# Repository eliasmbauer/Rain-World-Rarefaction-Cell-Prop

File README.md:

# Rain World Rarefaction Cell Interactive Prop

Notice: This project is currently unfinished, and will be updated regularly until it's completion.

In this folder you should find everything you need to get started with assembling this project yourself.  
`setup.pdf` should contain the step-by-step instructions to build this project from scratch using the design files provided.  
Consider `README.md` as a folder hierarchy list, as well as a description of what exactly this is for those of you unfamiliar with the video game *Rain World*.

# What is it?

This project is a physical recreation of the Rarefaction Cell from the video game *Rain World*, an orb-like object that can alter the gravity of the character in-game.

# Folder Contents
- **setup.pdf** 
  A PDF containing the assembly instructions.

- **Rarefaction_Cell_Chassis** 
  A folder containing the stl files for the chassis, modeled after the in-game asset.

- **Refraction_Cell_Circuit_(Kicad)** 
  A folder containing the Gerber files necessary to edit and print the control board, as well as the files necessary for modifications.

- **Rarefaction_Cell_Firmware** 
  A folder containing firmware for flashing the onboard ESP32.

- **Refraction_Cell_Audio_Bytes**
  A folder containing all the audio samples and raw audio bytes used in this project.

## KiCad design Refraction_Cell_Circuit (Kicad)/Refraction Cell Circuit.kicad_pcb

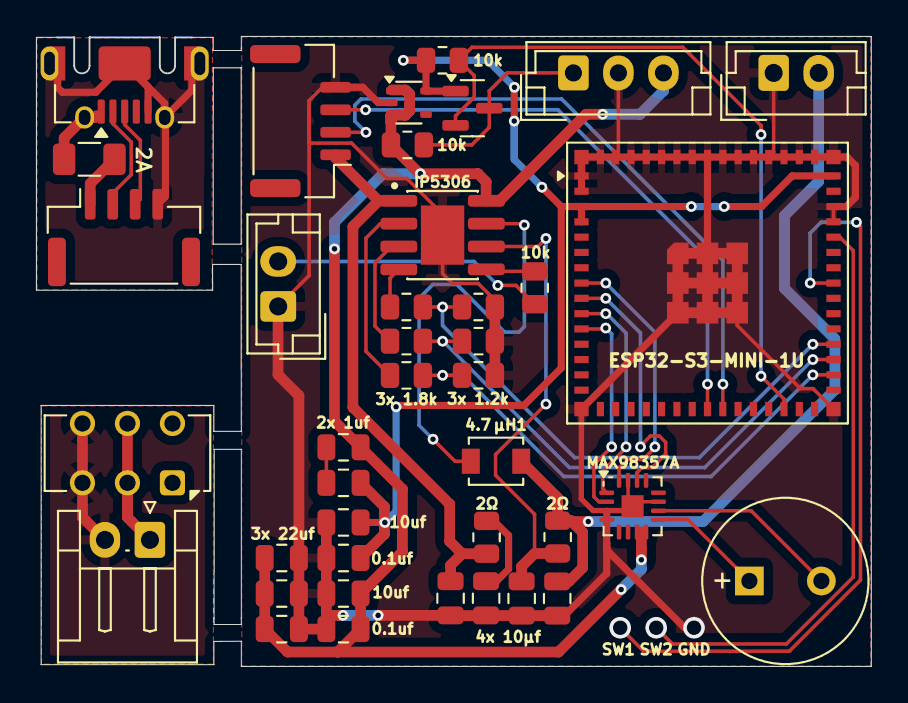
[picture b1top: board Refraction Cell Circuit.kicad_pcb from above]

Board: 2 copper layers, 46.3 x 35.0 mm, 32 parts (0 on the bottom side), 25 nets.

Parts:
2x 10µf: 10uf; C_0805_2012Metric
2Ω: 2; R_0805_2012Metric
3x 22uf: 22uf; C_0805_2012Metric
4.7 µH1: L; L_Wuerth_WE-GF-1210
10k: 10k; R_0805_2012Metric
10k#2: 100k; R_0805_2012Metric
C1, C2: 1uf; C_0805_2012Metric
C6, C8, C10, C11, C12: 10uf; C_0805_2012Metric
C7, C9: 0.1uf; C_0805_2012Metric
C15, C16: 22uf; C_0805_2012Metric
LS2: Speaker; MagneticBuzzer_PUI_AT-0927-TT-6-R
Q1: BSS138; SOT-23
R3, R5, R11: 1.8k; R_0805_2012Metric
R4, R10, R12: 1.2k; R_0805_2012Metric
R7: 2; R_0805_2012Metric
R14: 10k; R_0805_2012Metric
SW1: SW_DPDT_x2; SW_CK_JS202011AQN_DPDT_Angled
U1: ESP32-S3-MINI-1U; ESP32-S2-MINI-1U
U3: IP5306; SOIC9P127_490X600X170L84X42T330X241N
U4: MIC5365-3.3YC5; SOT-353_SC-70-5
U5: MAX98357A; TQFN-16-1EP_3x3mm_P0.5mm_EP1.23x1.23mm

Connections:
3.3V: 10k.1, C2.1, C6.1, C7.1, Q1.1 (G), U1.3 (3V3), U1.4 (IO0), U1.45 (EN), U4.5 (VOUT)
5V: 3x 22uf.1, C1.1, C8.1, C9.1, C15.1, C16.1, R14.1, U3.8 (VOUT), U4.1 (VIN), U4.3 (EN), U5.7 (VDD), U5.8 (VDD)
5V-PWR-SW: 10k#2.2, SW1.2 (B), SW1.5
5V-SOURCE: C10.1, R7.1, U3.1 (VCC)
BCLK: U1.8 (IO4), U5.16 (BCLK)
Bat Indicator 1 (3.3V): R3.1, R4.2, U1.32 (IO36)
Bat Indicator 1 (5V): R3.2, U3.2 (LED1)
Bat Indicator 2 (3.3V): R5.1, R10.2, U1.33 (IO37)
Bat Indicator 2 (5V): R5.2, U3.3 (LED2)
Bat Indicator 3 (3.3V): R11.1, R12.2, U1.34 (IO38)
Bat Indicator 3 (5V): R11.2, U3.4 (LED3)
Bat+: 2x 10µf.1, 2Ω.1, 4.7 µH1.2
Bat-: 2x 10µf.2, 3x 22uf.2, C6.2, C7.2, C8.2, C9.2, C10.2, C11.2, C12.2, C15.2, C16.2, R4.1, R10.1, R12.1, SW1.5, U1.1 (GND), U1.2 (GND), U1.42 (GND), U1.43 (GND), U1.46 (GND), U1.47 (GND), U1.48 (GND), U1.49 (GND), U1.50 (GND), U1.51 (GND), U1.52 (GND), U1.53 (GND), U1.54 (GND), U1.55 (GND), U1.56 (GND), U1.57 (GND), U1.58 (GND), U1.59 (GND), U1.60 (GND), U1.61 (GND), U1.62 (GND), U1.63 (GND), U1.64 (GND), U1.65 (GND), U3.9 (GND), U4.2 (GND), U5.3 (GND), U5.4 (~SD_MODE), U5.11 (GND), U5.15 (GND), U5.17 (PAD)
DOUT: U1.10 (IO6), U5.1 (DIN)
GAIN: U1.11 (IO7), U5.2 (GAIN_SLOT)
LED Com (3.3V): 10k.2, Q1.2 (S), U1.28 (IO33)
LED Com (5v): Q1.3 (D), R14.2
LRCK: U1.9 (IO5), U5.14 (LRCLK)
unnamed: C1.2, C2.2
unnamed: C11.1, R7.2
unnamed: 2Ω.2, C12.1, U3.6 (BAT)
unnamed: 10k#2.1, U3.5 (KEY)
unnamed: 4.7 µH1.1, U3.7 (SW)
unnamed: LS2.2, U5.10 (OUTN)
unnamed: LS2.1, U5.9 (OUTP)

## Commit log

2025-05-02 First Commit: added the chassis and circuit prototypes to the project
2025-05-02 some formatting changes
2025-05-02 more formatting changes
2025-05-04 Quick Spelling Fix For README.md
2025-05-04 Seperated the stl file into seperatefiles reqiring different types of fillament
2025-05-05 added a firmware file with pin definitions, as well as slight modifications to the schematic
2025-05-13 included gerber files
2025-05-13 fixed gerber files
